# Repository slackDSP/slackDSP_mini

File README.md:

# slackDSP_mini

[YouTube demo video](http://www.youtube.com/watch?v=F_a12EcQlmA)

Nothing to see here yet....

<br>

### Resources
* [dsPIC33FJ128GP804 datasheet](http://ww1.microchip.com/downloads/en/DeviceDoc/70292G.pdf)
* [Wolfson WM8510 datasheet](https://www.cirrus.com/en/pubs/proDatasheet/WM8510_v4.5.pdf)
* [23LC1024 datasheet](http://ww1.microchip.com/downloads/en/DeviceDoc/20005142C.pdf)
* [MPLABX IDE download page](http://www.microchip.com/pagehandler/en-us/family/mplabx/home.html)
* [XC16 compiler download page](http://www.microchip.com/pagehandler/en-us/devtools/mplabxc/home.html)

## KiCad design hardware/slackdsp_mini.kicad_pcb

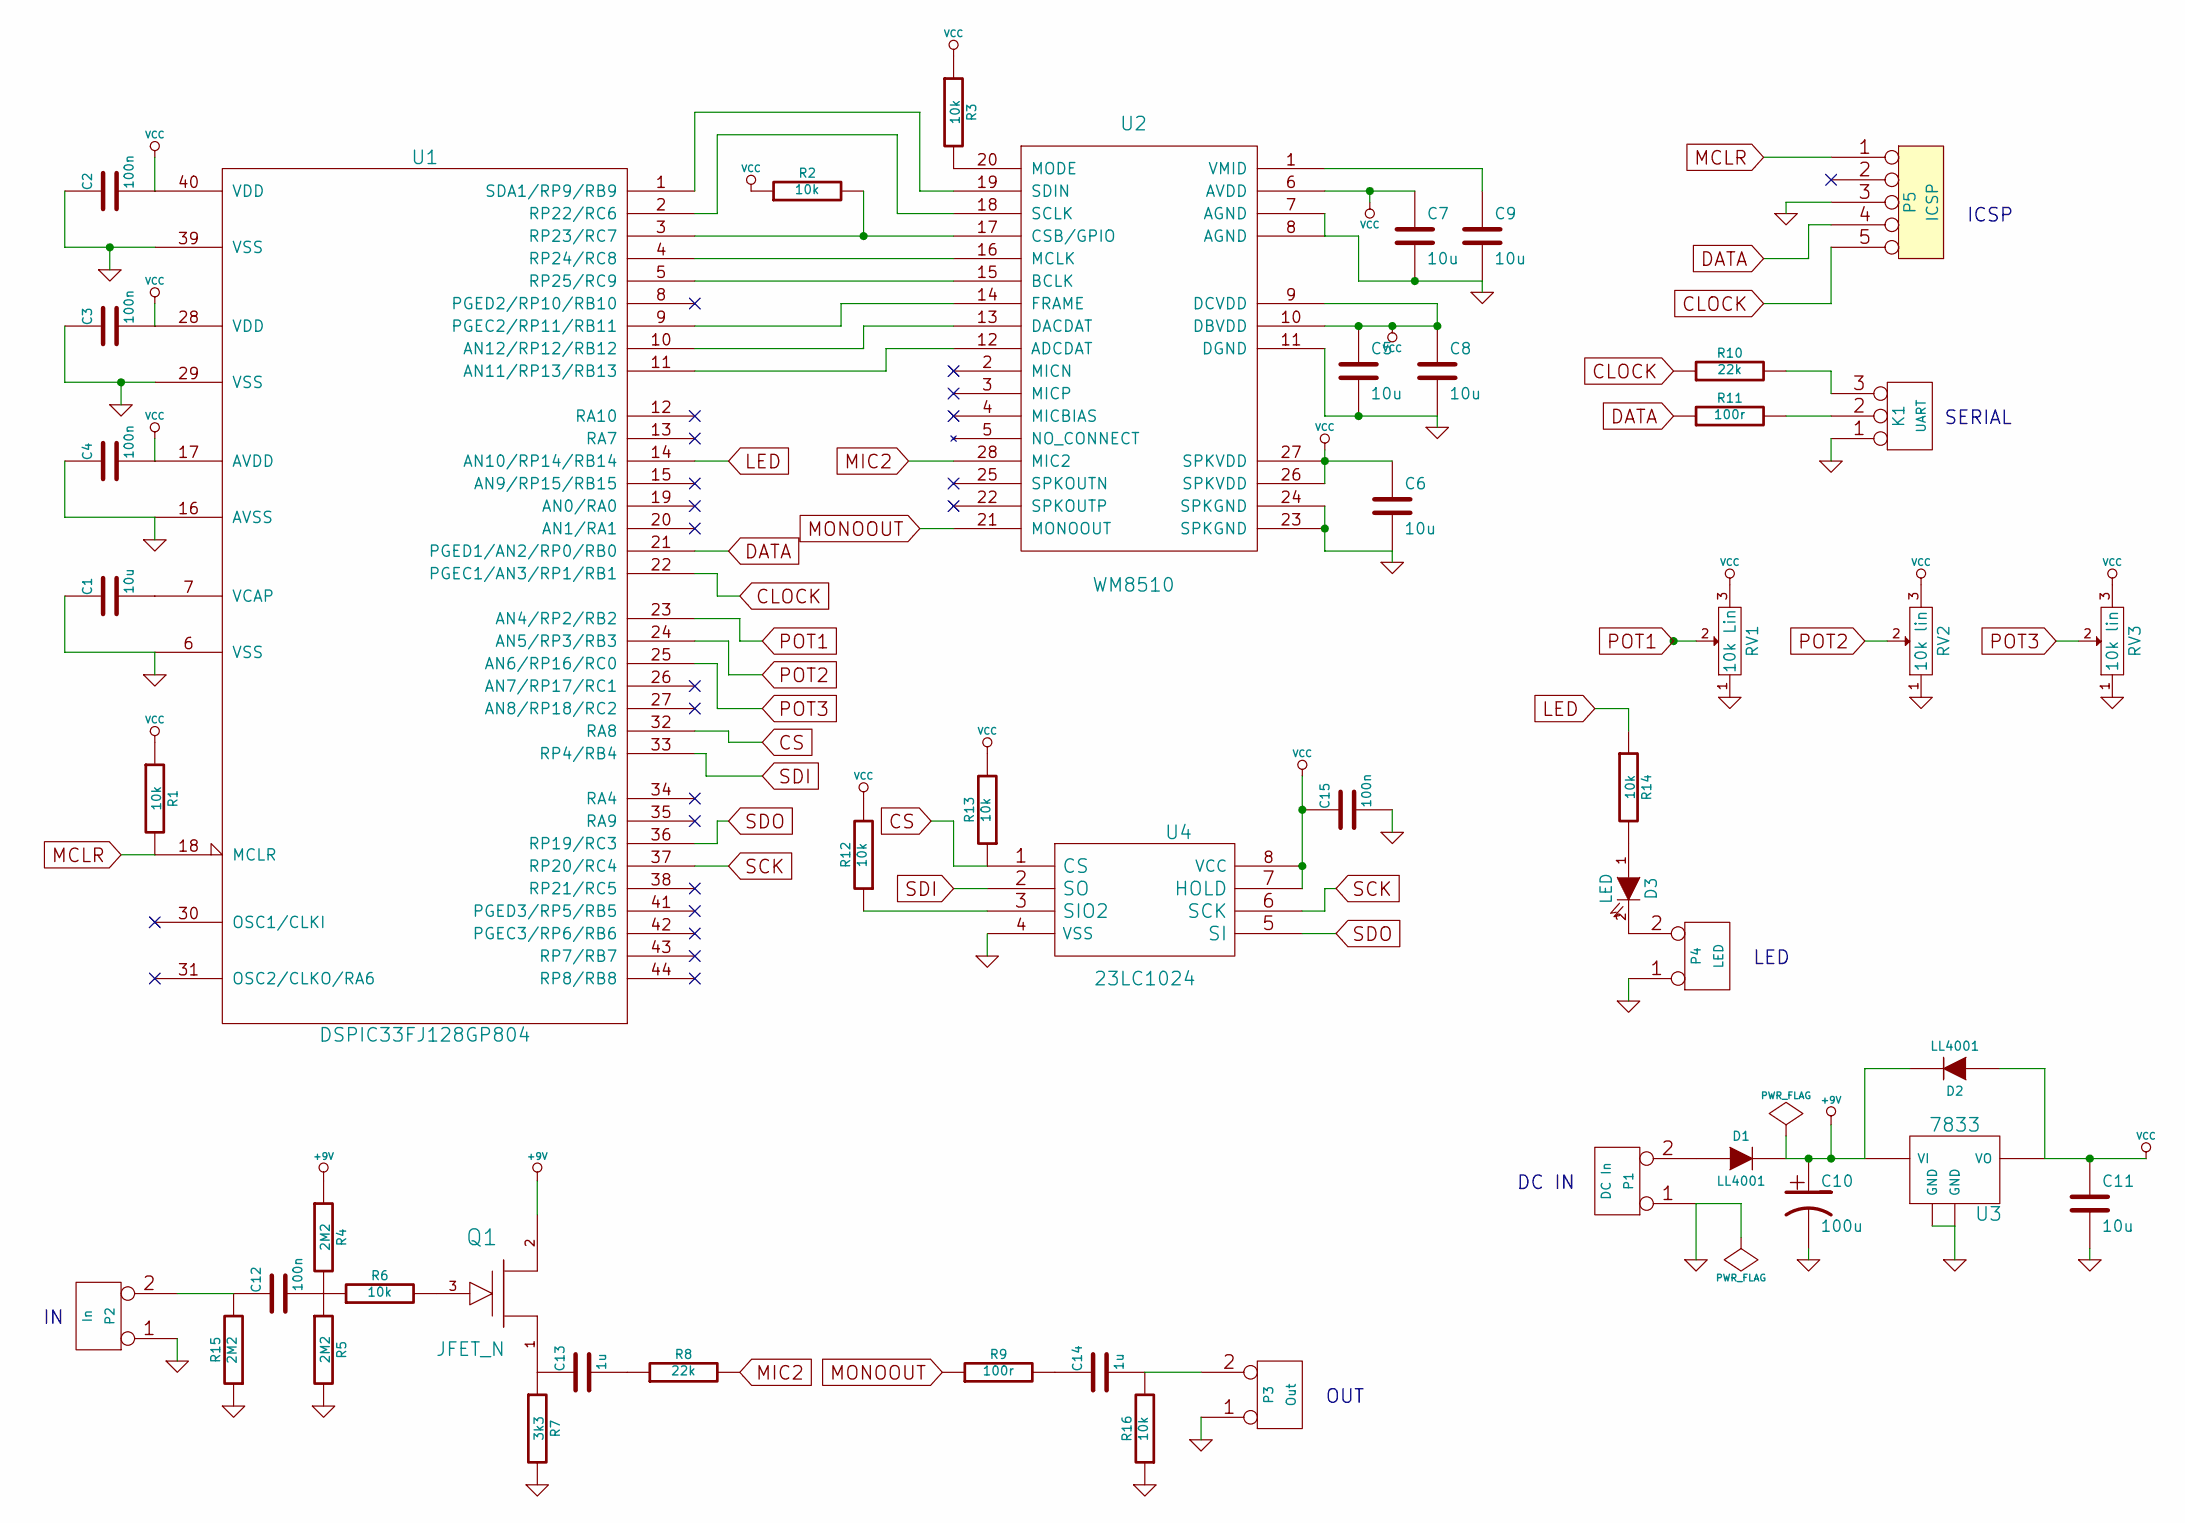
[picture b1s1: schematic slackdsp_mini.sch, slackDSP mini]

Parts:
C1, C5, C6, C7, C8, C9, C11: 10u; C_1210_HandSoldering
C2, C3, C4, C12, C15: 100n; C_1206
C10: 100u; CP_Radial_D5.0mm_P2.50mm
C13, C14: 1u; C_1206
D1, D2: LL4001; C_1812
D3: LED; LED_D3.0mm
K1: UART; Pin_Header_Straight_1x03_Pitch2.54mm
P1: DC In; Pin_Header_Straight_1x02_Pitch2.54mm
P2: In; Pin_Header_Straight_1x02_Pitch2.54mm
P3: Out; Pin_Header_Straight_1x02_Pitch2.54mm
P4: LED; Pin_Header_Straight_1x02_Pitch2.54mm
P5: ICSP; Pin_Header_Straight_1x05_Pitch2.54mm
Q1: JFET_N; SOT-23
R1, R2, R3, R6, R12, R13, R14, R16: 10k; R_1206
R4, R5, R15: 2M2; R_1206
R7: 3k3; R_1206
R8, R10: 22k; R_1206
R9, R11: 100r; R_1206
RV1: 10k Lin; POT_16mm
RV2, RV3: 10k lin; POT_16mm
U1: DSPIC33FJ128GP804; TQFP-44_10x10mm_Pitch0.8mm
U2: WM8510; SSOP-28_5.3x10.2mm_Pitch0.65mm
U3: 7833; SOT-223
U4: 23LC1024; SO8-Narrow

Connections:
+9V: C10.1, D1.2 (K), D2.2 (K), Q1.2 (D), R4.1, U3.1 (VI)
CLOCK: P5.5, R10.1, U1.22 (PGEC1/AN3/RP1/RB1)
CS: R13.1, U1.32 (RA8), U4.1 (CS)
DATA: P5.4, R11.1, U1.21 (PGED1/AN2/RP0/RB0)
GND: C1.1, C2.1, C3.1, C4.1, C5.2, C6.2, C7.2, C8.2, C9.2, C10.2, C11.2, C15.2, K1.1, P1.1, P2.1, P3.1, P4.1, P5.3, R5.2, R7.2, R15.1, R16.1, RV1.1, RV2.1, RV3.1, U1.6 (VSS), U1.16 (AVSS), U1.29 (VSS), U1.39 (VSS), U2.7 (AGND), U2.8 (AGND), U2.11 (DGND), U2.23 (SPKGND), U2.24 (SPKGND), U3.2 (GND), U3.4 (GND), U4.4 (VSS)
LED: R14.1, U1.14 (AN10/RP14/RB14)
MCLR: P5.1, R1.2, U1.18 (MCLR)
MIC2: R8.2, U2.28 (MIC2)
MONOOUT: R9.1, U2.21 (MONOOUT)
unnamed: C1.2, U1.7 (VCAP)
unnamed: C9.1, U2.1 (VMID)
unnamed: C12.1, P2.2 (PM), R15.2
unnamed: C12.2, R4.2, R5.1, R6.1
unnamed: C13.1, Q1.1 (S), R7.1
unnamed: C13.2, R8.1
unnamed: C14.1, R9.2
unnamed: C14.2, P3.2 (PM), R16.2
unnamed: D1.1 (A), P1.2 (PM)
unnamed: D3.1 (A), R14.2
unnamed: D3.2 (K), P4.2 (PM)
unnamed: K1.2 (PM), R11.2
unnamed: K1.3, R10.2
unnamed: Q1.3 (G), R6.2
unnamed: R2.2, U1.3 (RP23/RC7), U2.17 (CSB/GPIO)
unnamed: R3.2, U2.20 (MODE)
unnamed: R12.1, U4.3 (SIO2)
unnamed: U1.1 (SDA1/RP9/RB9), U2.19 (SDIN)
unnamed: U1.2 (RP22/RC6), U2.18 (SCLK)
unnamed: U1.4 (RP24/RC8), U2.16 (MCLK)
unnamed: U1.5 (RP25/RC9), U2.15 (BCLK)
unnamed: U1.9 (PGEC2/RP11/RB11), U2.14 (FRAME)
unnamed: U1.10 (AN12/RP12/RB12), U2.13 (DACDAT)
unnamed: U1.11 (AN11/RP13/RB13), U2.12 (ADCDAT)
POT1: RV1.2, U1.23 (AN4/RP2/RB2)
POT2: RV2.2, U1.24 (AN5/RP3/RB3)
POT3: RV3.2, U1.25 (AN6/RP16/RC0)
SCK: U1.37 (RP20/RC4), U4.6 (SCK)
SDI: U1.33 (RP4/RB4), U4.2 (SO)
SDO: U1.36 (RP19/RC3), U4.5 (SI)
VCC: C2.2, C3.2, C4.2, C5.1, C6.1, C7.1, C8.1, C11.1, C15.1, D2.1 (A), R1.1, R2.1, R3.1, R12.2, R13.2, RV1.3, RV2.3, RV3.3, U1.17 (AVDD), U1.28 (VDD), U1.40 (VDD), U2.6 (AVDD), U2.9 (DCVDD), U2.10 (DBVDD), U2.26 (SPKVDD), U2.27 (SPKVDD), U3.3 (VO), U4.7 (HOLD), U4.8 (VCC)

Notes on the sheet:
ICSP
SERIAL
OUT
DC IN
LED

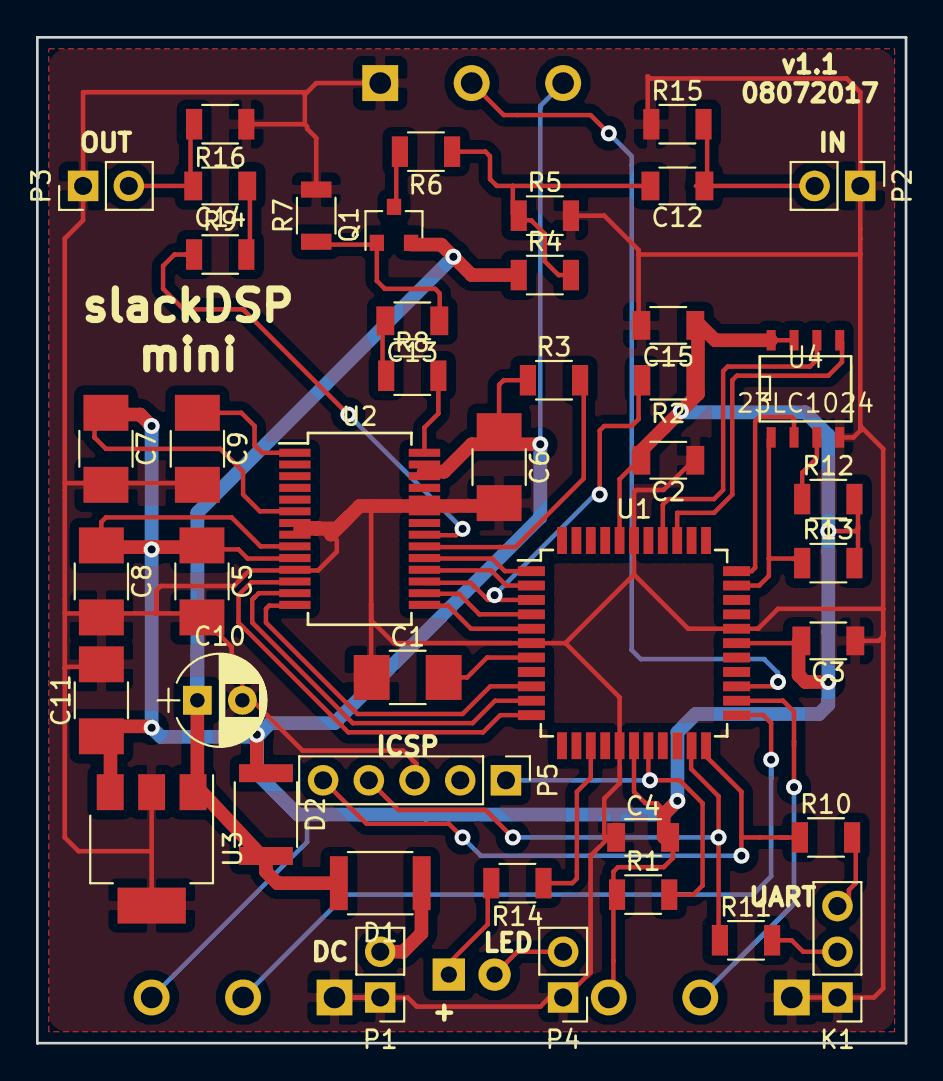
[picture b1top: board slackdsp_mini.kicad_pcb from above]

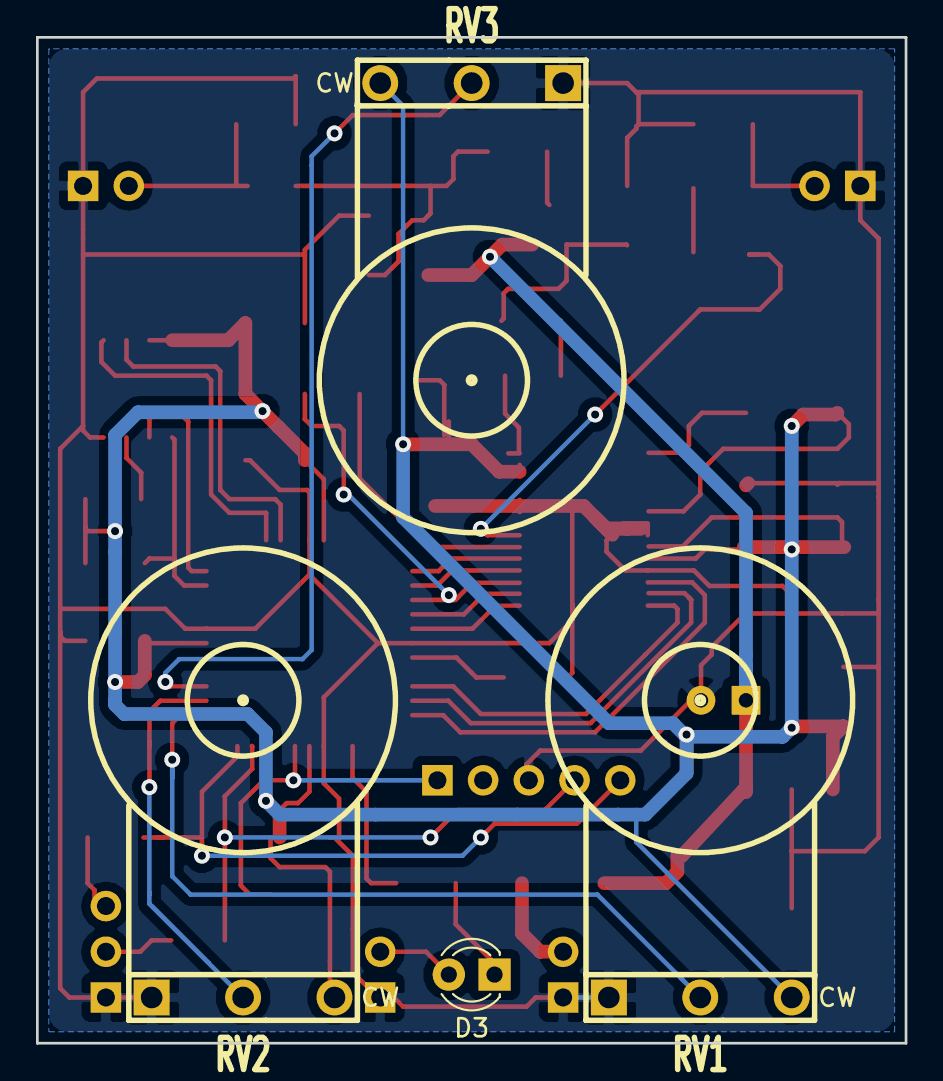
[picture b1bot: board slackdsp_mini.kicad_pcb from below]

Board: 2 copper layers, 48.3 x 55.9 mm, 48 parts (4 on the bottom side), 40 nets.

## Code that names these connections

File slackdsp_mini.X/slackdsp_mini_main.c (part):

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    RPO24 = OC2_out; //RP24 (pin 4) = PWM CLOCKOUT
    RPO9 = SDO1_out; //RP5 (pin 14) = SDO1
    RPO22 = SCK1_out; //RP6 (pin 15) = SCK1
    TRISCbits.TRISC7 = 0; //RC7 (Pin 16) = output = WM8510_SS (SPI slave select)
    RPO19 = SDO2_out; //RP19 (pin 36) = SDO2
    RPO20 = SCK2_out; //RP20 (pin 27) = SCK2
    SDI2_in = RPI4; //RP4 (pin 33) = SDI2
    TRISAbits.TRISA8 = 0; //RA8 (Pin 32) = output = sram_SS (SPI slave select)
    CSCK_in = RPI25; //RP9 (pin 18) = CSCLK << BCLCK
    COFS_in = RPI11; //RP10 (pin 21) = COFS << FRAME
    CSDI_in = RPI13; //RP12 (pin 23) = CSDI << ADCDAT
    RPO12 = CSDO_out; //RP11 (pin 22) = CSDO >> DACDAT

    TRISBbits.TRISB14 = 0;
    AD1PCFGLbits.PCFG4 = 0; //Set AN4 (pin 23) analogue = POT1
    AD1PCFGLbits.PCFG5 = 0; //Set AN5 (pin 24) analogue = POT2
    AD1PCFGLbits.PCFG6 = 0; //Set AN6 (pin 25) analogue = POT3

    //Initialise DCI module
    DCICON1bits.CSCKD = 1; //CSCK is an input
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
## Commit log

2015-03-02 updated .gitignore
2015-03-02 cleaned up .gitignore
2015-03-18 here we go
2015-03-18 Added source code
2015-03-19 updated source code
2015-04-21 Added effect examples
2015-04-28 added www folder
2015-04-30 Added licence info
2015-04-30 amended licence info
2015-04-30 renamed src folder
2015-05-18 renamed folders
2015-05-31 Renamed kicad files
2015-05-31 Amended schematic
2015-06-04 Fixed some typos and stuff
2015-10-25 tweaks
2017-08-20 Added licence
2017-08-20 Updated PCB

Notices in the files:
hardware/slackdsp_mini.sch:
© Ian Maltby 2014
